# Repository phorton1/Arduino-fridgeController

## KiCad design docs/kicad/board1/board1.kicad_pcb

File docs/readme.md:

# fridgeController - for Danfoss BD35/BD50 w/12V Inverter

**Home** --
**[Design](design.md)** --
**[Electronics](electronics.md)** --
**[Build](build.md)** --
**[Notes](notes.md)** --
**[Analysis](analysis.md)**

The original **Waeco Adler Barbour Cold Machine Board F-1886 Rev2** used on
my boat's refrigeration system burned out.  It has failed several
times, and from the beginning, and over the 17 years I have had the boat,
I have jury rigged solutions for controlling the temperature of the freezer,
having indicator lights that I can see, and so forth.

The compressor is a **Danfoss BD50** and uses the typical **12V Inverter Module**
to actually run the compressor.  For many years I fought with water cooling the
refrigerator, but after changing many hoses and pumps, over and over, I decided
to just let it be air cooled.

In any case I have decided to trash the original controller board and wiring harness,
and build my own **ESP32** based **Thermostat and Controller** using my
[**myIOT**](https://github.com/phorton1/Arduino-libraries-myIOT)
architecture to also provide a consistent **WebUI** and remote monitoring capabilities.

The circuit will NOT include a relay to control a water cooling pump, but that
could easily be added.

Unfortunately there are no schematics of the Danfoss Inverter and so I have had
to [reverse engineer](analysis.md) it's behavior empirically.   I have two different units.
There is an **101N0212** currently on the pump.  I also have a spare **101N0220**
I used for reverse engineering on my desk (without a compressor).

## A. Documentation Organization

The documentation of the fridgeController is broken up into several pages:

- **home** - this page, which includes an Overview of the design
- **[Design](design.md)** - detailed design, including parameters & behavior
- **[Electronics](electronics.md)** - circuit schematics and PCB's
- **[Build](build.md)** - 3D printing, assembly, and installation
- **[Notes](notes.md)** - Implementation Notes for the fridgeController
- **[Analysis](analysis.md)** - A *detailed analysis* of the **101N0212/101N0220 Danfoss/Secop**
  Inverter behavior.

## B. Design Overview

Physically, I have decided to break the physical design into two
circuits.  Each part will have a PCB and a 3D printed box..

The first part is the **miniBox** which is relatively simple, and
which will sit atop the inverter in a 3D printed enclosure.  The
second part will be the more complicated ESP32 based **Controller**
which will live in a kitchen cabinet and have an external WS2812b
LED.

### miniBox

The **miniBox** is intended to remain in place and be testable,
and nominally usable, without the controller being present.
It allows the compressor to be run via **2 switches**, at low or
high speed in the event the ESP32 based controller fails,
or is not present (i.e. in development or being repaired).
It has the following connectors:

- has a **2 pin Phoenix plug** for 12V input from the
  inverter's main BATT+ and BATT- terminals
- has a **2 pin Phoenix plug** for FAN+ and FAN- output
  to the 12V 0.6A FAN
- has a **6 pin JST connector** for input from the other 6 terminals
  (FAN/DIODE+, FAN-, DIODE-, C, P, and T) from the inverter
- has an **8 pin JST connector** for output to the ESP32 based
  controller

The miniBox has three indicator LEDs

- **GREEN** to show when the inverter box generally has power.
- **YELLOW** to show when the FAN is on.
- **RED** for the flashing diagnostic diode.

The miniBox has two switches that allow the compressor to
be run in an emergency, in the absence of a controller, or
generally, to override the controller.

- **OVERRIDE** - Turns the pump on, overriding the (possibly missing)
  controller.
- **LOW/HIGH SPEED** - Controls the speed of the compressor if
  OVERRIDE is turned on.

As mentioned before, the compressor can be run and used
with just the miniBox.  In the event that it fails for some
reason, it may quickly be removed, and as long as the main
12V power supply to the inverter is supplied, the compressor can be
run at low speed by merely shorting the T&C pins on the
inverter.

### Controller

The Controller sits in a cabinet out of view.
It is based on an **ESP32** and has **WIFI Connectivity**
The Controller has the following connectors:

- a **2 pin JST connector** for the **12V power supply** input for the Controller.
- a **6 pin JST connector** for the other 6 pins of the 8 pin cable
  **from the miniBox**.
- two **3 pin JST connectors** for connecting **DS18B20 temperature
  sensors**
- a single **2 pin JST connector** for connection to an optional
  **mechanical thermostat**
- a **3 pin JST connector** for output to external **WS2812B
  LED*s** that can be mounted on the controller, and/or outside
  of the cabinet for a general visual indication of the state
  of the system and inverter/compressor.

Initially the Controller will be powered by breaking the BATT+ and
BATT- wires of the 8 pin cable from the miniBox into a separate 2 pin
JST connector.  Later, if so desired, the Controller can be powered
by a separate connection to the boat's batteries so that the Inverter
power supply can be turned off and on as needed without necessarily
rebooting the ESP32, thus allowing the Controller to detect and alert
me to refrigerator power problems,

The Controller generally has a number of physical features:

- **on/off switch**
- 16x2 character **Blue LCD** display
- an **SD Card** for storing refrigerator **history** and **logfiles**
- three **buttons** for direct programming of the Controller
- four **indicator LEDs** (green, yellow, red, and blue)

The Controller can be programmed (temperature cutoffs, general
configuration) using the 3 buttons and the LCD screen.
In addition, or perhaps primarily, though, it will have a
**Web User Interface** that can be accessed from a phone,
laptop, or other programs on the boat's LAN, and will function
as a **myIOT** device.

## Please Also See

This project directly makes direct use of my
[**MyIOT**](https://github.com/phorton1/Arduino-libraries-myIOT)
("my internet of things*) repository, which provides a generalized approach to
building relatively simple parameter driven ESP32 devices that include a Web UI.

The PCBs (printed circuit boards) were **milled** using the
[**cnc3018**](https://github.com/phorton1/Arduino-esp32_cnc3018) CNC
machine that I built.

I hope you will take a few minutes to check out some of these other pages too!!

## Credits

This project directly relies upon the public open source Arduino development system,
the Espressif ESP32 online documentation and additions to the Arduino IDE, as
well as a number open source Arduino libraries

I would like to thank the countless individuals who have contributed to making these
development tools, source codes, and documentation available for free public use, including,
but not limited to:

- [KiCad](https://www.kicad.org/)
- [FlatCAM](https://bitbucket.org/jpcgt/flatcam/downloads/) by **Juan Pablo Caram**
- [Arduino IDE and Libraries](https://www.arduino.cc/)
- [Espressif Systems](https://www.espressif.com/en/products/socs/esp32)
- [Adafruit NeoPixel Library](https://github.com/adafruit/Adafruit_NeoPixel)
- **jQuery**, **Bootstrap**, and the [jqPlot](Xhttp://www.jqplot.com/) javascript libraries

## License

This program, project, and repository is free software: you can redistribute it and/or modify
it under the terms of the GNU General Public License Version 3 as published by
the Free Software Foundation.

These materials are distributed in the hope that they will be useful,
but WITHOUT ANY WARRANTY; without even the implied warranty of
MERCHANTABILITY or FITNESS FOR ANY PARTICULAR PURPOSE.  See the
GNU General Public License for more details.

Please see [LICENSE.TXT](../LICENSE.TXT) for more information.

[**Next:**](design.md) A look at the detailed design of the fridgeController ...

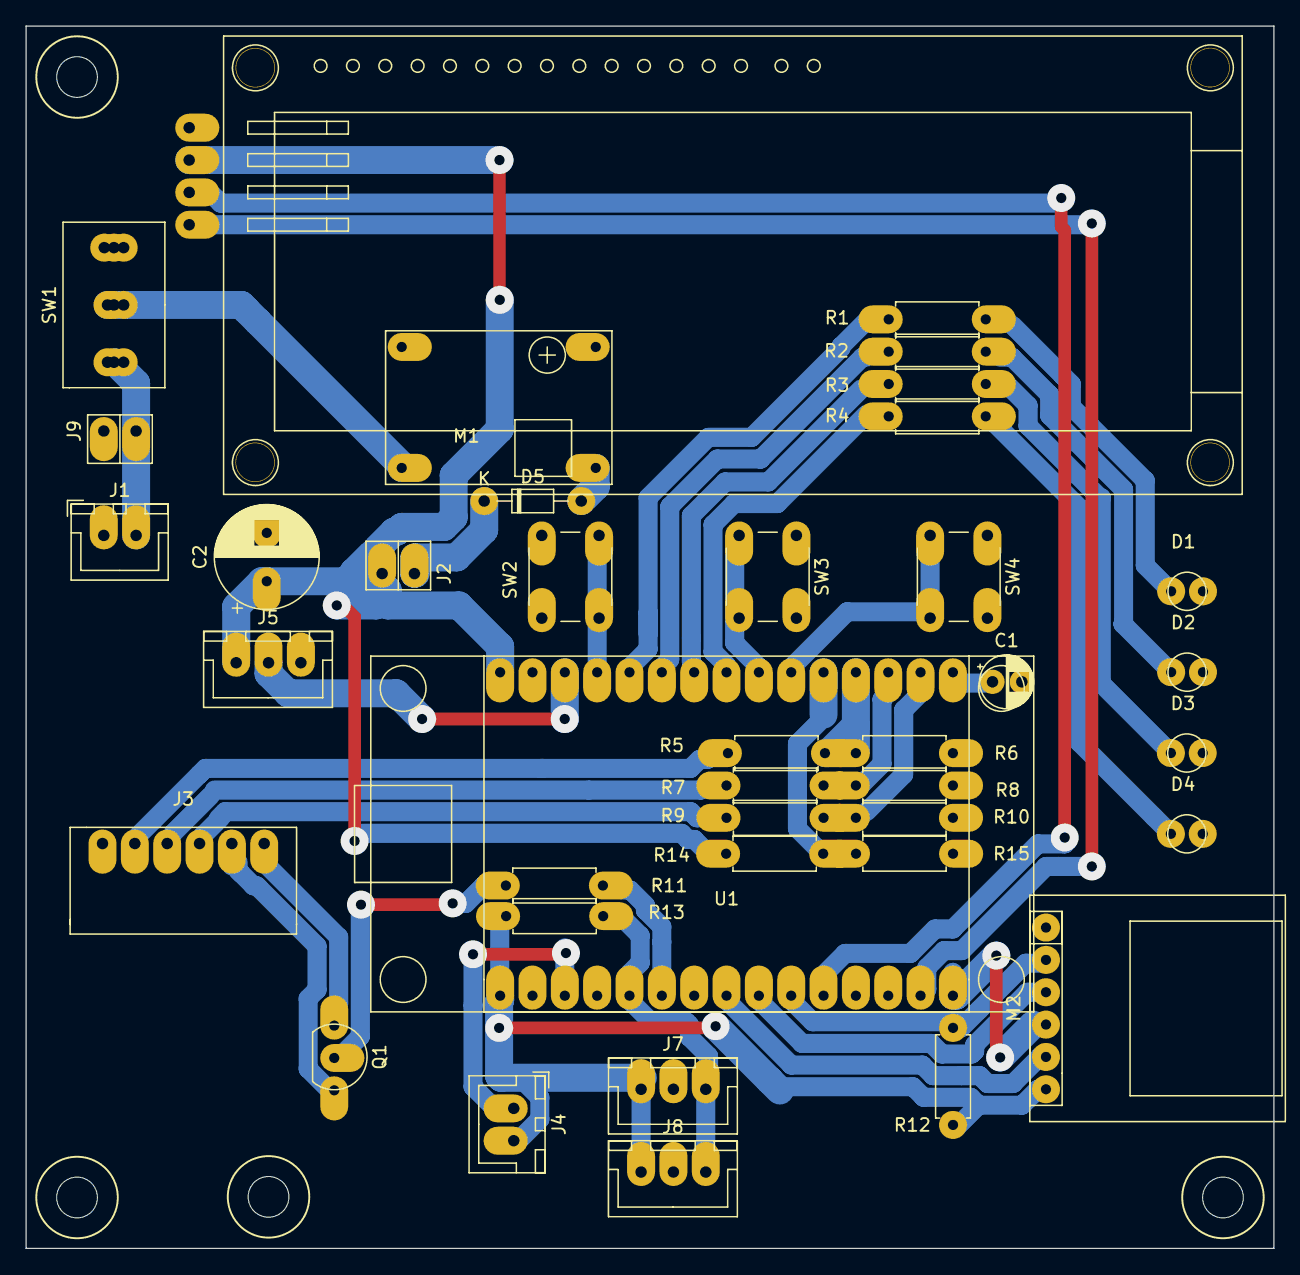
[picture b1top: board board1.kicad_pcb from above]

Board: 2 copper layers, 98.0 x 96.0 mm, 39 parts (0 on the bottom side), 39 nets.

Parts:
C1: 4.7uf; CP_my10uf
C2: 100uf; CP_my100uf
D1: GREEN; led_small_green
D2: YELLOW; led_small_yellow
D3: RED; led_small_red
D4: BLUE; led_small_blue
D5: 1N4003; myZenerDiode
J1: 12V_IN; myJSTx02
J2: 5V_JUMP; pinHeader1x2
J3: MINI_BOX; myJST6_right
J4: MECH_THERM; myJSTx02
J5: EXT_LED; JST3
J6: LCD; myLCD_2x16
J7: TEMP1; JST3
J8: TEMP2; JST3
J9: 12V_TEST; pinHeader1x2
M1: BUCK01; buck-mini360
M2: SD_TYP0; SDCardReader
Q1: BC547; transistor
R1, R2, R3, R4: 220; resistor
R5, R7, R9, R12, R14: 10K; resistor
R6, R8, R10: 2K; resistor
R11, R13, R15: 4.7K; resistor
SW1: ON/OFF; SW_DPDT_BLUE_LEVER
SW2: BUTTON1; button_6mm_H12
SW3: BUTTON2; button_6mm_H12
SW4: BUTTON3; button_6mm_H12
U1: ESP32_DEV_0; esp32_dev_0

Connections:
+3V3: J4.2, J7.1, J8.1, M2.6, R12.1, R13.1, U1.30
+5V: C2.1, J2.2, J5.1, J6.2, R14.2, U1.1
BUTTON1: SW2.2, U1.4
BUTTON2: SW3.2, U1.9
BUTTON3: SW4.2, U1.10
C: J3.5, Q1.3
DIAG_DIODE: J3.4, R9.2
EXT_LED: J5.2, U1.3
FAN-: J3.3, R7.2
FAN_DIODE+: J3.2, R5.2
GND: C1.2, C2.2, D1.1, D2.1, D3.1, D4.1, J1.1, J3.1, J5.3, J6.1, J7.2, J8.2, J9.1, M1.1, M1.2, M2.1, R6.1, R8.1, R10.1, R15.1, SW2.1, SW3.1, SW4.1, U1.2, U1.29
LED_BLUE: R4.2, U1.8
LED_GREEN: R1.2, U1.5
LED_RED: R3.2, U1.7
LED_YELLOW: R2.2, U1.6
MECH_THERM: J4.1, U1.28
MISO: M2.2, R12.2, U1.21
MOSI: M2.4, U1.16
unnamed: C1.1, U1.15
unnamed: D1.2, R1.1
unnamed: D2.2, R2.1
unnamed: D3.2, R3.1
unnamed: D4.2, R4.1
unnamed: D5.1, J2.1
unnamed: D5.2, M1.3
unnamed: J1.2, SW1.3
unnamed: M1.4, SW1.2
unnamed: Q1.2, R11.2
ONE_WIRE: J7.3, J8.3, R13.2, U1.26
PWM: R11.1, U1.25
SCL: J6.4, U1.17
SCLK: M2.3, U1.22
SDA: J6.3, U1.20
SD_CS: M2.5, U1.23
S_5V: R14.1, R15.2, U1.11
S_DIODE: R9.1, R10.2, U1.14
S_FAN: R7.1, R8.2, U1.13
S_PLUS: R5.1, R6.2, U1.12
T: J3.6, Q1.1

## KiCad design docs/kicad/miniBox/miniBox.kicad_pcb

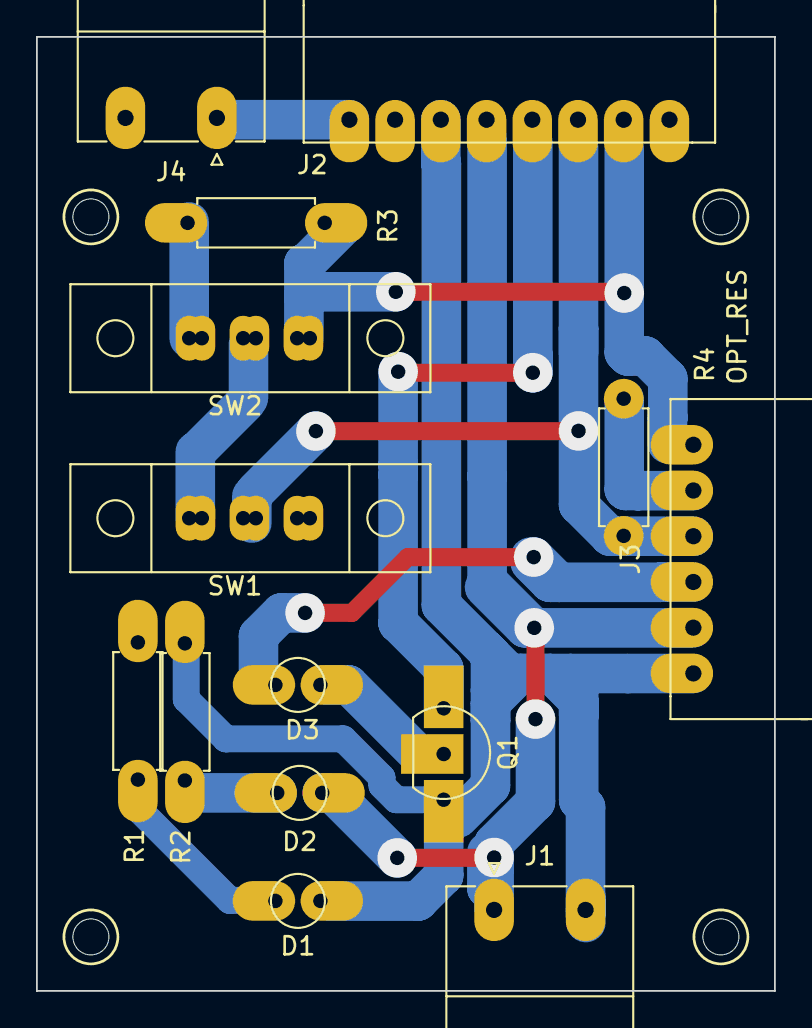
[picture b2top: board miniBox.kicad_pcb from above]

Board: 2 copper layers, 41.0 x 53.0 mm, 14 parts (0 on the bottom side), 14 nets.

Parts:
D1: GREEN; led_small_green
D2: YELLOW; led_small_yellow
D3: RED; led_small_red
J1: FAN; PhoenixContact_MC_1,5_2-G-5.08_1x02_P5.08mm_Horizontal
J2: CONTROLLER; myJST8_right
J3: INV_CONN; myJST6_right
J4: INV_PWR; PhoenixContact_MC_1,5_2-G-5.08_1x02_P5.08mm_Horizontal
Q1: BC557 PNP; transistor
R1: 1K; resistor
R2, R3: 1.5K; resistor
R4: 10K?; resistor
SW1: OVERRIDE; SlideSPDT_small
SW2: LOW/HIGH; SlideSPDT_small

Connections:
+12V: J2.8, J4.1
C: J2.3, J3.4, R4.2, SW1.2
DIAG_DIODE: J2.4, Q1.1
DIODE-: D3.1, J3.3
FAN-: D2.1, J1.1, J2.5, J3.2
FAN_DIODE+: D1.2, J1.2, J2.6, J3.1, Q1.3, R2.1
GND: J2.1, J2.7, J4.2, R1.1
unnamed: D1.1, R1.2
unnamed: D2.2, R2.2
unnamed: D3.2, Q1.2
unnamed: R3.2, SW2.3
unnamed: SW1.3, SW2.2
P: J3.5, R4.1
T: J2.2, J3.6, R3.1, SW2.1

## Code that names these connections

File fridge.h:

//----------------------------------------------
// constants for fridgeController
//----------------------------------------------
// uses ESP32 standard SPI mosi(23) miso(19) sclk(18)
// and I2C scl(22) sda(21)

#pragma once

#include <myIOTDevice.h>

#define WITH_PWM	1


//=========================================================
// pins
//=========================================================

#define PIN_PUMP_PWM		16		// PWM sent to BC547 transistor tween C2 and T from inverter
#define PIN_EXT_LED			13		// external WS2812b LED(s)
#define PIN_ONE_WIRE		4		// One-Wire bus to DS18B20 temperature probes
#define PIN_MECH_THERM		15		// Sense the (old) Danfoss mechanical thermostat

#define PIN_BUTTON1			12
#define PIN_BUTTON2			33
#define PIN_BUTTON3			32

#define PIN_S_PLUS			34		// sense FAN/DIODE+ proxy for 12V
#define PIN_S_FAN			39		// sense FAN- low when fan running
#define PIN_S_DIODE 		36		// sense DIODE- made HIGH with BC557 transistor when diag diode on
#define PIN_S_5V			35		// sense buck 5V power supply

#define PIN_LED_RED			26		// diagnostic diode on
#define PIN_LED_GREEN		14		// have power
#define PIN_LED_BLUE		25		// compressor on
#define PIN_LED_YELLOW		27		// fan on

#define LED_COMPRESS_ON		PIN_LED_BLUE
#define LED_DIODE_ON 		PIN_LED_RED
#define LED_POWER_ON		PIN_LED_GREEN
#define LED_FAN_ON			PIN_LED_YELLOW


#define PWM_CHANNEL				0
#define PWM_FREQ				5000
#define PWM_RESOLUTION			8


//------------------------
// myIOT definition
//------------------------

#define FRIDGE_CONTROLLER			"fridgeController"
#define FRIDGE_CONTROLLER_VERSION	"fc0.2"
#define FRIDGE_CONTROLLER_URL		"https://github.com/phorton1/Arduino-boat-fridgeController"

#define BACKLIGHT_ALWAYS_ON			120

#define MIN_SETPOINT_DIF	2.0		// centigrade


// enumerated FRIDGE_MODE types & ids

#define FRIDGE_MODE_OFF				0
#define FRIDGE_MODE_RUN_MIN			1
#define FRIDGE_MODE_RUN_MAX			2
#define FRIDGE_MODE_RUN_USER		3
#define FRIDGE_MODE_RUN_MECH		4
#define FRIDGE_MODE_RUN_TEMP		5

// main fridge config/state values

#define ID_FRIDGE_MODE				"FRIDGE_MODE"
#define ID_SETPOINT_HIGH            "SETPOINT_HIGH"
#define ID_SETPOINT_LOW             "SETPOINT_LOW"
#define ID_USER_RPM                 "USER_RPM"
#define ID_MIN_RPM                  "MIN_RPM"
#define ID_MAX_RPM                  "MAX_RPM"
#define ID_FRIDGE_SENSE_ID          "FRIDGE_SENSE_ID"
#define ID_COMP_SENSE_ID            "COMP_SENSE_ID"
#define ID_EXTRA_SENSE_ID           "EXTRA_SENSE_ID"
#define ID_TEMP_SENSE_SECS          "TEMP_SENSE_SECS"
#define ID_INV_SENSE_MS         	"INV_SENSE_MS"
#define ID_CALIB_VOLTS_INV          "CALIB_VOLTS_INV"
#define ID_CALIB_VOLTS_5V           "CALIB_VOLTS_5V"

#define ID_CLEAR_ERROR				"CLEAR_ERROR"

#define ID_STATUS					"STATUS"
#define ID_FRIDGE_TEMP              "FRIDGE_TEMP"
#define ID_COMP_TEMP                "COMP_TEMP"
#define ID_EXTRA_TEMP               "EXTRA_TEMP"
#define ID_MECH_THERM               "MECH_THERM"
#define ID_COMP_RPM                 "COMP_RPM"
#define ID_INV_ERROR                "INV_ERROR"
#define ID_INV_PLUS                 "INV_PLUS"
#define ID_INV_FAN                  "INV_FAN"
#define ID_VOLTS_INV				"VOLTS_INV"
#define ID_VOLTS_5V					"VOLTS_5V"

// fridge UI config/state values

#define ID_BACKLIGHT_SECS			"BACKLIGHT_SECS"
#define ID_LED_BRIGHTNESS			"LED_BRIGHTNESS"

#define ID_CHART_LINK				"CHART"




extern enumValue fridgeModes[];
	// in fridgeController.ino


class Fridge : public myIOTDevice
{
public:

    Fridge();
    ~Fridge() {}

    virtual void setup() override;
    virtual void loop() override;

    // fridge config values

	static int 		_fridge_mode;
	static int 		_user_rpm;
	static int		_min_rpm;
	static int		_max_rpm;
	static String	_fridge_sense_id;
	static String	_comp_sense_id;
	static String	_extra_sense_id;
	static int		_temp_sense_secs;
	static int		_inv_sense_ms;
	static float	_setpoint_high;
	static float	_setpoint_low;
	static float	_calib_volts_inv;
	static float	_calib_volts_5v;

	// fridge state values

	static String	_status_str;
	static float	_fridge_temp;
	static float	_comp_temp;
	static float	_extra_temp;
	static bool 	_mech_therm;
	static int		_comp_rpm;
	static int		_inv_error;
	static bool		_inv_plus;
	static bool		_inv_fan;
	static bool		_inv_compress;
	static float	_volts_inv;
	static float	_volts_5v;

	// ui config/state values

	static int		_backlight_secs;
	static int		_led_brightness;
	static String 	_chart_link;

	// public states available to other objects

	static bool		m_log_error;			// low level error calling myIOTDataLog::addRecord()
	static int 		m_fridge_temp_error;	// low level error getting fridge temperature
	static int 		m_comp_temp_error;		// low level error getting compressor temperature
	static int 		m_extra_temp_error;		// low level error getting extra temperature
	static bool		m_force_pixels;			// to force pixels redraw in onSetBrightness()

	// raw sensor values for logging

	static int16_t	m_raw_fridge_temp;
	static int16_t	m_raw_comp_temp;
	static int16_t	m_raw_extra_temp;

	// methods

	void setRPM(int rpm);
	void stateMachine();
	static void stateTask(void *param);
	static void onSetPointChanged(const myIOTValue *value, float val);
	static void onBacklightChanged(const myIOTValue *value, int val);
	static void onBrightnessChanged(const myIOTValue *desc, uint32_t val);
	static void clearInvError();
		// clears the DIAG flashing LED when FRIDGE_MODE==OFF
		// by toggling the PWM on for 1/2 second. See implementation.

	// extensions
	
	String onCustomLink(const String &path,  const char **mime_type) override;
    virtual bool hasPlot() override    { return true; }


};


extern Fridge *fridge;





//=========================================================
// external utilities
//=========================================================

extern int rpmToDuty(int rpm);
	// in fridge.cpp

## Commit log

2024-09-08 add unused S_5V pin to kicad/board1 ESP32
2024-09-08 initial factoring; implemented DS18B20 OneWire temperature sensor based on Arduino DallasTemperature library
2024-09-08 initial factor Arduino-frigeController to myIOT
2024-09-13 produced fridgeController pcb's "board1" and "miniBox"
2024-09-13 initial fridgeController lcd sscreen
2024-09-15 sanity checkin - back from foray into Arduino2, ESP32S3, ESP32 Cores 1_0_6 and 3_0_4, munged /AppData/Local/Arduino15 directory Most of these changes revolve around anticipating issues if and when I 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
2024-09-15 minor changes before more testing ArduinoIDE2.3.3 and Esp32Core3.0.4 on LENOVO-T490-2
2024-09-16 added build_opt.h which has no effect in IDE 1.18.3, but potentially replaces setup_platform.pm in IDE 2.3.2
2024-09-17 added .gitignore of preferences.txt
2024-09-17 preferences.txt and .gitignore changes on LENOVO-T490-2
2024-09-17 remove from git
2024-09-17 reduce memory for chart for testing
2024-09-17 restore test plot memory usage
2024-09-17 initial documentation organization
2024-09-18 initial implementation of in-memory dataLog.h, lots of testing of jqPlot, check source for jqPlot in /js
2024-09-19 better chart auto_scaling algorithm - API still needs work
2024-09-20 added actual SD card dataLogging with - rudimentary seconds "period" based UI - enhancedLegendRenderer allows toggling of series display - reverse order of canvases so 0 is on top - bringing series t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
2024-09-21 working on fridgeController documentation
2024-09-21 moved jqplot JS to main myIOT data submodule
2024-09-21 first simple Widget prototype testing; WIP on fridgeController, onCustomLink() idea, caching, and charting
2024-09-21 submodule(data) auto_commit(83767cf1) Added a Widget tab to the main myIOT webpage; added jqplot CSS and JS files; wrote iotPlot.js prototype of charting within a "widget" - see fridgeController chec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
2024-09-21 moved fridgeController::dataLog object to myIOTDataLogger
2024-09-21 WIP on JS/CSS and general caching in myIOT web server
2024-09-22 myIOT Widets II - introduce basic HTTP caching; refactor myIOT iotPlot.js into iotCommon.js, cleanup Widget concepts and code; sanity checkcin
2024-09-22 submodule(data) auto_commit(0465efe4) myIOT Widets II - introduce basic HTTP caching; refactor myIOT iotPlot.js into iotCommon.js, cleanup Widget concepts and code; sanity checkcin
2024-09-22 submodule(data) auto_commit(e76456cf) iotPlot.js - minor change to Fix Zooming; otherwise "comments only"
2024-09-23 renamed iotPlot.js to iotChart.js with consistent method names
2024-09-24 created a WS based Plotter!
2024-09-24 submodule(data) auto_commit(86b02898) created a WS based Plotter!
2024-09-25 submodule(data) auto_commit(331f60b7) refined myIOT plotter with LEGENDS and using device specific PLOT_TYPES if available; theClock3 implementation of PLOT_CYCLES and PLOT_WAVES
2024-09-25 added legend to INO (plotting in vSense.cpp)
2024-09-26 prep for bilgeAlarm bar chart widget - reworked myIOTDataLog to send records from back of file until dt stamp is met, which required myIOTWebServer to use HTTP 1.0 to send binary data with unknown co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
2024-09-26 submodule(data) auto_commit(68039dc2) prep for bilgeAlarm bar chart widget - reworked myIOTDataLog to send records from back of file until dt stamp is met, which required myIOTWebServer to use HTTP 1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
2024-09-27 reworked bilgeAlarm to use simplified myIOTDataLog and rely on SD card. changed WIP fridgeController as a result
2024-09-29 added prototype bilgeAlarm jqPlot Widget using added "alt_data_format" and custom chart_header and chart_data code in onCustomLink(). modified myIOT/data index.html, iotChart.js, and iotCommon.js
2024-09-29 submodule(data) auto_commit(416ed000) added prototype bilgeAlarm jqPlot Widget using added "alt_data_format" and custom chart_header and chart_data code in onCustomLink(). modified myIOT/data index.h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
2024-10-01 Initial actual DESIGN, IMPLEMENTATION, and new fakeCompressor
2024-10-01 submodule(data) auto_commit(2407a228) added global DEGREE_TYPE and VALUE_STYLE_TEMPERATURE, supprted in webUI, dataLog, and Charts
2024-10-01 enough messing with the fakeCompressor - gotta do some real stuff
2024-10-01 debugging only
2024-10-02 implement initial uiScreen (only missing static POWER screen)
2024-10-03 implement display VOLTAGE - vSense sampling, fridgepublishing, uiScreen, & fakeCompressor & design documentations
2024-10-04 READY TO TRY bench inverter with new cable, changes include - comments - moved COMP_ON BLUE LED logic to setRPM() - More work around with fakeCompressor - turned off /custom/chart_data myIOTHTTP debu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
2024-10-06 added WITH_PWM global define and ID_CLEAR_ERRORS command
2024-10-06 kicad - miniBox - corrected routing of FAN DIODE from FAN- to FAN/DIODE+ instead of GND
2024-10-06 kicad - board1 - rerouted 5V to LCD; added backflow prevention diode to 5V jumper
2024-10-06 first 3D print of miniBox
2024-10-06 submodule(data) auto_commit(28556b88) iotCommon.js - changed keep_alive timings and const's to vars to allow debugging at runtime
2024-10-07 change chart column names to "fridge" and "comp"
2024-10-07 documentation WIP - broke out analsys.md, cleanup and spellcheck, add first images
2024-10-07 submodule(data) auto_commit(f3e2065d) reduce size of WS status fields in index.html
2024-10-08 allow CLEAR_ERROR command while FRIDGE_MODE; added CLEAR_ERROR to uiScreen.cpp (doesn't show if no INV_ERROR)
2024-10-08 doc WIP - cleanup CLEAR_ERROR semantics; start build.md; spell-check
2024-10-08 checkin Fusion 360, Prusa, and Lightburn output after main 3D printing and Laser work;
2024-10-10 update documentation; add webUI tooltips
2024-10-10 minor Fusion mods to reprint clear plastic lenses and controllerBox
2024-10-10 add tooltips, external WS2812b pixels; ID_LED_BRIGHTNESS; re-calibrate voltages, general cleanup before installation
2024-10-10 submodule(data) auto_commit(b622c3ba) Use regular javascript alert instead of myAlert and hide progress on upload_error
2024-10-11 Doc WIP - notes.md updated with brief Charting & Logging section
2024-10-11 grrr - re-print controllerBox due to lack of cutouts
2024-10-11 final pre-install documentation
2024-10-11 last minute changes - stupid "Cover Clips"
2024-10-12 temporary fix to temp_chart.html; fix minor documentation typos
2024-10-14 vSense.cpp - USER CIRCULAR BUFFER FOR VOLTAGES; was getting random diode errors
2024-10-16 change fridgeChart RPM interval to 1000
2024-10-16 Added doc notes about initial observations and design thoughts after running fridge for 4 days
2024-10-18 added EXT_LED box and 3rd pixel; changed bootup LED and PIXEL displays; experimented with SSD1306 OLED displays
2024-10-19 add better resizing to iotChart.js
2024-10-19 add Arduino-tempController to github
2024-10-19 minor debug and UI fixes
2024-10-19 submodule(data) auto_commit(c0e7ba5a) add better resizing to iotChart.js
2024-10-21 resize temp_chart.html
2024-10-21 submodule(data) auto_commit(b811e3f8) move generic uiButtons to myIOTButtons; implement initial tempController uiScreen and PCB board(s)
2024-10-24 normalized fridgeController to use myIOT Temperature sensor and Buttons; rename objects in fridgeController and tempController for consistency and name space separation.
2024-10-25 submodule(data) auto_commit(fdbad871) fix myIOTServer with new chart stuff (pass uuids, caching, etc)
2024-10-25 updated temp_chart.html to set and use device_uuid
2024-10-30 chnage Arduino-libraries-myIOT/myTempSensor to myIOTTempSensor to allow for a "my" version that is currently not on github
2025-12-15 submodule(data) auto_commit(b649fc3a) iotChart.js - added scheme for setting device specific series colors
2025-12-17 myIOT cleanup - got rid of Widget implementations
2025-12-18 submodule(data) auto_commit(1adaeb45) reworked iotChart.js incremental update scheme starting with Arduino-boat-drainPump
2025-12-18 submodule(data) auto_commit(b6ac0c88) starting in Arduino-boat-arirco, major rework of iotChart.js and how charts are implemented - use common chart.html instead of specific/extra_data/device_chart.h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
2025-12-18 submodule(data) auto_commit(1efc7b72) rework iotChart.js::determineNumberTicks() starting with drain_pump
2025-12-18 submodule(data) auto_commit(78894e93) change onChartResize() to use create_chart() instead of built in jqplot.replot()
2025-12-18 submodule(data) auto_commit(40916b0c) separate iotChart.js doChart() as init only method from onXXX() UI methods - yet another rework of iotChart.js and myIOTDataLog starting with fridgeController
2025-12-18 submodule(data) auto_commit(b923e44d) back to static html for chart.html; got rid of myIOTDataLog::getChartHtml() starting with tempController
2025-12-18 bring up to latest data/iotChart.js and data/chart.html
2025-12-18 submodule(data) auto_commit(a4e2ed81) change chart.html and iotChart.js to use and remove style "degree_hidden" for devices that chart things with degrees
2025-12-18 submodule(data) auto_commit(a9754dbc) fixed renamed control _degree_type
2025-12-18 submodule(data) auto_commit(03555741) fix malformed chart.html <select id='_chart_period'> text
2025-12-19 submodule(data) auto_commit(1cb3d61a) add onChartResize() back to chart.html
2025-12-19 submodule(data) auto_commit(253976a9) more changes to iotChart.js starting with tempController so at least refresh works *well* if no zooming involved
2025-12-19 commit parents
2025-12-20 submodule(data) auto_commit(eccd1fcc) iotChart.js - added save/restore of series visibility and refactored code
2025-12-23 got rid of gitignore for preferences.txt
2025-12-31 submodule(data) auto_commit(2a8db875) add degree_type to myIOT chart_header for use in initializing iotChart.js
2026-02-22 myIOTHTTP.cpp: added special case to do token replacement for "data_name" in chart.html AND updated myIOT devices with charts to pass data_name in chart_link
2026-02-22 submodule(data) auto_commit(37a6a76c) added framework for chart.html to pass "data_name" to allow multiple charts per device; ALSO store most recent chart period in browser storage
2026-03-04 added smaller (UINT8, CENTIGRADE8, UINT8x10) iotDataLog LOG_TYPES and updated client ctors
2026-03-04 submodule(data) auto_commit(75bcbcb5) iotChart.js - added smaller (UINT8, CENTIGRADE8, UINT8x10) iotDataLog LOG_TYPES and updated client ctors
2026-03-04 added myIotTempSensor "raw" accessors & used to shrink fridgeController.dataLog file size; got rid of FAKE_COMPRESSOR
2026-03-04 submodule(data) auto_commit(d6f02205) added myIotTempSensor "raw" accessors & used to shrink fridgeController.dataLog file size; got rid of FAKE_COMPRESSOR
2026-03-04 got rid of dubious ability to turn myIOT WIFI off and on
2026-03-05 added "boat" to the myIOTDevice advertised SSDP device URL
2026-03-05 remove forward and lateral references to myIOT "bilgeAlarm" repo
2026-03-05 submodule(data) auto_commit(ecc76888) update myIOT data submodule readme.md to remove forward references to actual implmented device repos
2026-03-07 comments only
2026-03-07 submodule(data) auto_commit(5dbe3136) Save chart visibility and zorders in locsl storage
